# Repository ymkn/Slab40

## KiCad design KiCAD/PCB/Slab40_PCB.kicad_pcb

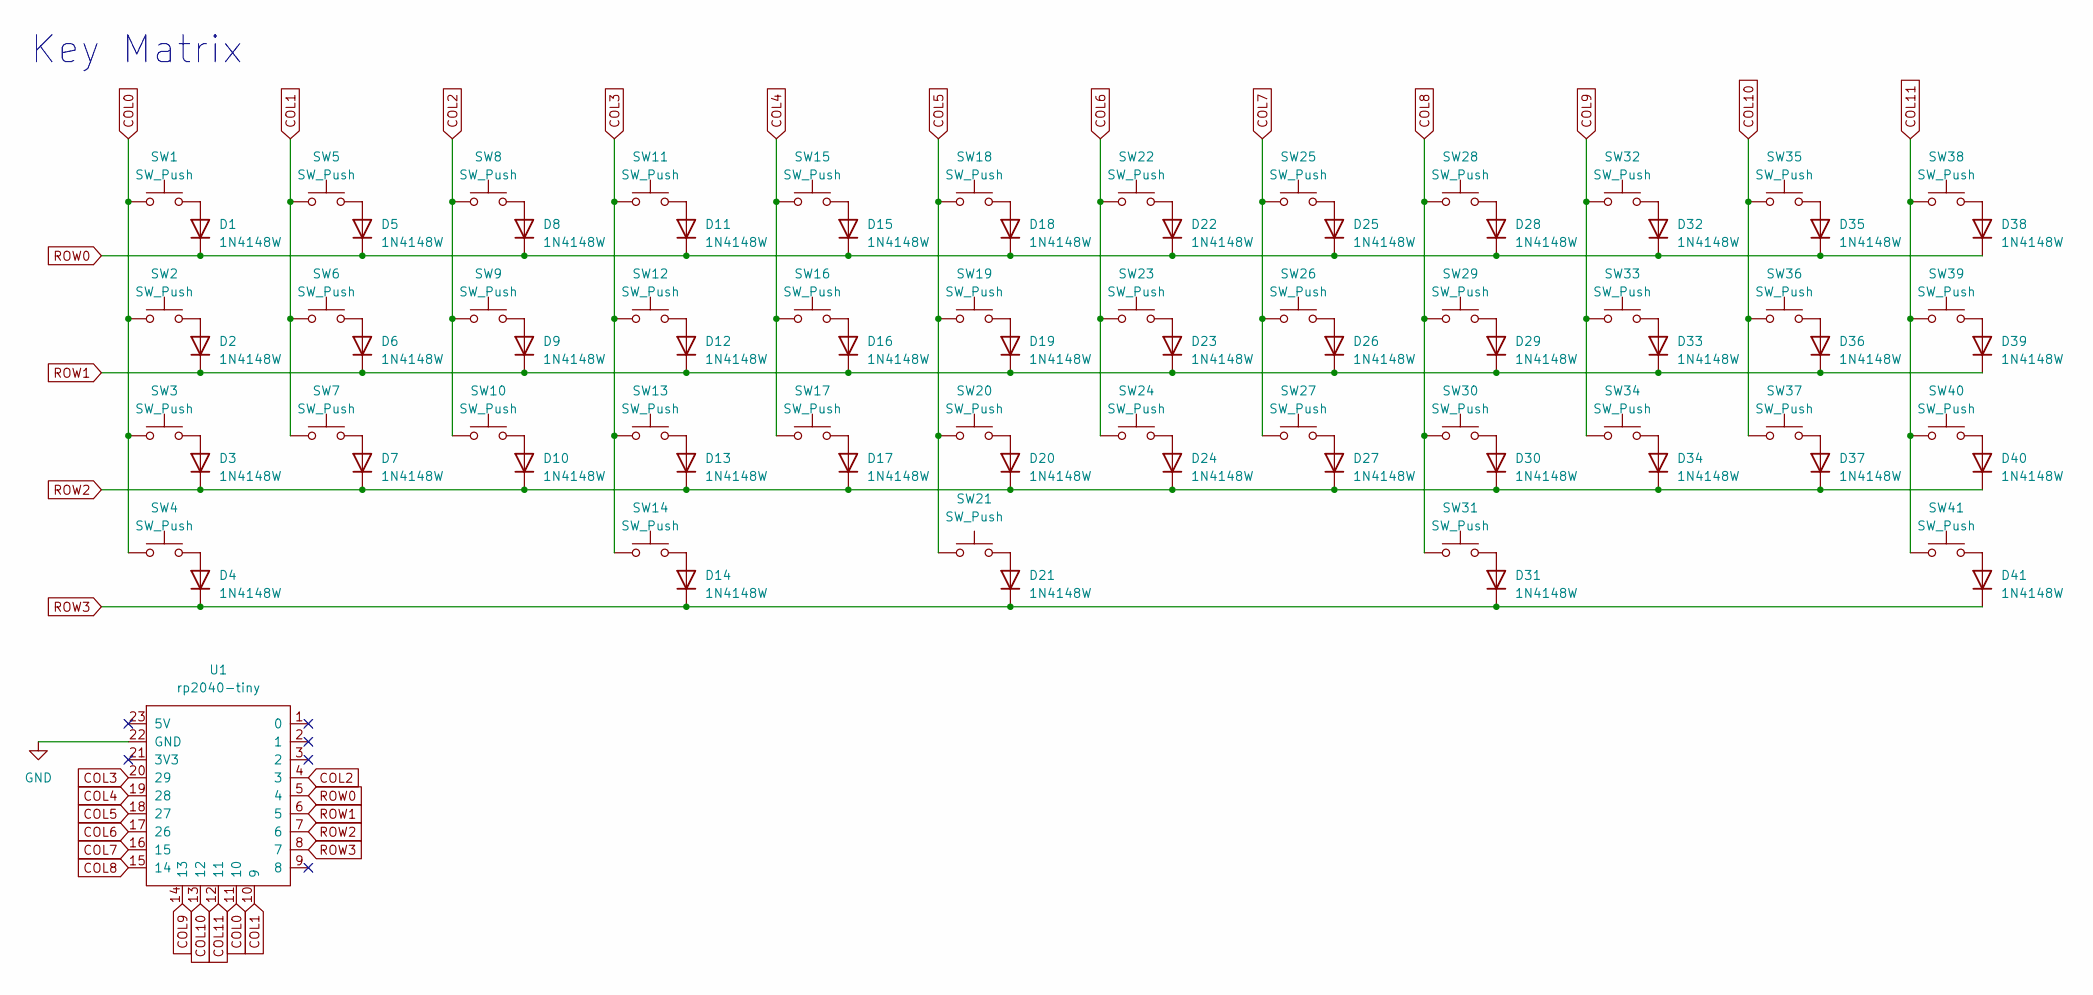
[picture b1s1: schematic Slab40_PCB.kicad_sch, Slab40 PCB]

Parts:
D1, D2, D3, D4, D5, D6, D7, D8, D9, D10, D11, D12, D13, D14, D15, D16, D17, D18, D19, D20, D21, D22, D23, D24, D25, D26, D27, D28, D29, D30, D31, D32, D33, D34, D35, D36, D37, D38, D39, D40, D41: 1N4148W; D_SOD-123; LCSC Parts # C81598
SW1, SW40: SW_Push; SW_MX_HS_CPG151101S11_1.25u
SW2, SW4, SW39, SW41: SW_Push; SW_MX_HS_CPG151101S11_1.5u
SW3, SW38: SW_Push; SW_MX_HS_CPG151101S11_1.75u
SW5, SW6, SW7, SW8, SW9, SW10, SW11, SW12, SW13, SW14, SW15, SW16, SW17, SW18, SW19, SW20, SW21, SW22, SW23, SW24, SW25, SW26, SW27, SW28, SW29, SW30, SW31, SW32, SW33, SW34, SW35, SW36, SW37: SW_Push; SW_MX_HS_CPG151101S11_1u
U1: rp2040-tiny; rp2040-tiny-smd

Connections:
COL0: SW1.1, SW2.1, SW3.1, SW4.1, U1.11 (10)
COL1: SW5.1, SW6.1, SW7.1, U1.10 (9)
COL2: SW8.1, SW9.1, SW10.1, U1.4 (3)
COL3: SW11.1, SW12.1, SW13.1, SW14.1, U1.20 (29)
COL4: SW15.1, SW16.1, SW17.1, U1.19 (28)
COL5: SW18.1, SW19.1, SW20.1, SW21.1, U1.18 (27)
COL6: SW22.1, SW23.1, SW24.1, U1.17 (26)
COL7: SW25.1, SW26.1, SW27.1, U1.16 (15)
COL8: SW28.1, SW29.1, SW30.1, SW31.1, U1.15 (14)
COL9: SW32.1, SW33.1, SW34.1, U1.14 (13)
COL10: SW35.1, SW36.1, SW37.1, U1.13 (12)
COL11: SW38.1, SW39.1, SW40.1, SW41.1, U1.12 (11)
GND: U1.22 (GND)
unnamed: D1.2 (A), SW1.2
unnamed: D2.2 (A), SW2.2
unnamed: D3.2 (A), SW3.2
unnamed: D4.2 (A), SW4.2
unnamed: D5.2 (A), SW5.2
unnamed: D6.2 (A), SW6.2
unnamed: D7.2 (A), SW7.2
unnamed: D8.2 (A), SW8.2
unnamed: D9.2 (A), SW9.2
unnamed: D10.2 (A), SW10.2
unnamed: D11.2 (A), SW11.2
unnamed: D12.2 (A), SW12.2
unnamed: D13.2 (A), SW13.2
unnamed: D14.2 (A), SW14.2
unnamed: D15.2 (A), SW15.2
unnamed: D16.2 (A), SW16.2
unnamed: D17.2 (A), SW17.2
unnamed: D18.2 (A), SW18.2
unnamed: D19.2 (A), SW19.2
unnamed: D20.2 (A), SW20.2
unnamed: D21.2 (A), SW21.2
unnamed: D22.2 (A), SW22.2
unnamed: D23.2 (A), SW23.2
unnamed: D24.2 (A), SW24.2
unnamed: D25.2 (A), SW25.2
unnamed: D26.2 (A), SW26.2
unnamed: D27.2 (A), SW27.2
unnamed: D28.2 (A), SW28.2
unnamed: D29.2 (A), SW29.2
unnamed: D30.2 (A), SW30.2
unnamed: D31.2 (A), SW31.2
unnamed: D32.2 (A), SW32.2
unnamed: D33.2 (A), SW33.2
unnamed: D34.2 (A), SW34.2
unnamed: D35.2 (A), SW35.2
unnamed: D36.2 (A), SW36.2
unnamed: D37.2 (A), SW37.2
unnamed: D38.2 (A), SW38.2
unnamed: D39.2 (A), SW39.2
unnamed: D40.2 (A), SW40.2
unnamed: D41.2 (A), SW41.2
ROW0: D1.1 (K), D5.1 (K), D8.1 (K), D11.1 (K), D15.1 (K), D18.1 (K), D22.1 (K), D25.1 (K), D28.1 (K), D32.1 (K), D35.1 (K), D38.1 (K), U1.5 (4)
ROW1: D2.1 (K), D6.1 (K), D9.1 (K), D12.1 (K), D16.1 (K), D19.1 (K), D23.1 (K), D26.1 (K), D29.1 (K), D33.1 (K), D36.1 (K), D39.1 (K), U1.6 (5)
ROW2: D3.1 (K), D7.1 (K), D10.1 (K), D13.1 (K), D17.1 (K), D20.1 (K), D24.1 (K), D27.1 (K), D30.1 (K), D34.1 (K), D37.1 (K), D40.1 (K), U1.7 (6)
ROW3: D4.1 (K), D14.1 (K), D21.1 (K), D31.1 (K), D41.1 (K), U1.8 (7)

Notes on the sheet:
Key Matrix

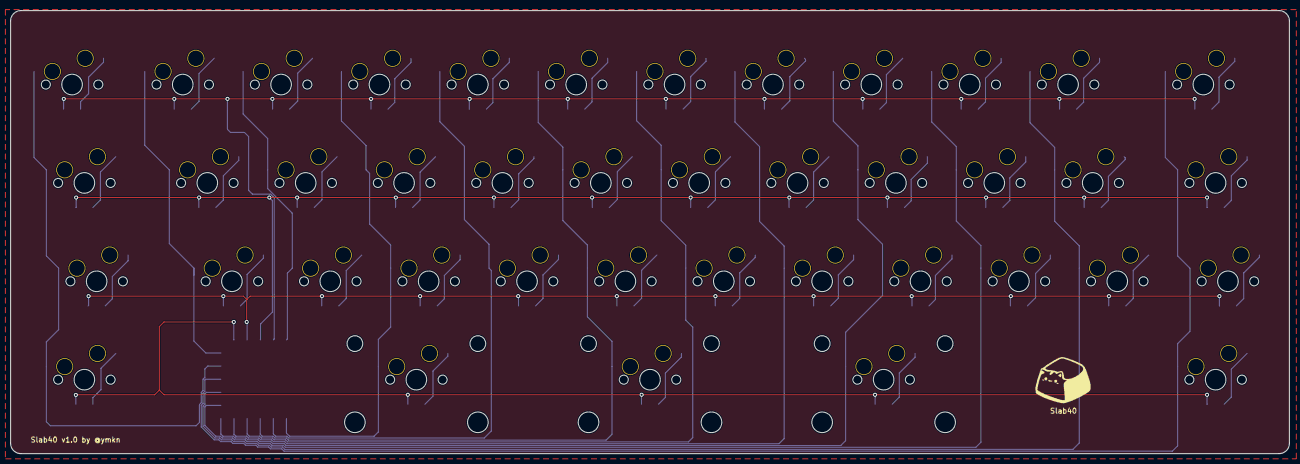
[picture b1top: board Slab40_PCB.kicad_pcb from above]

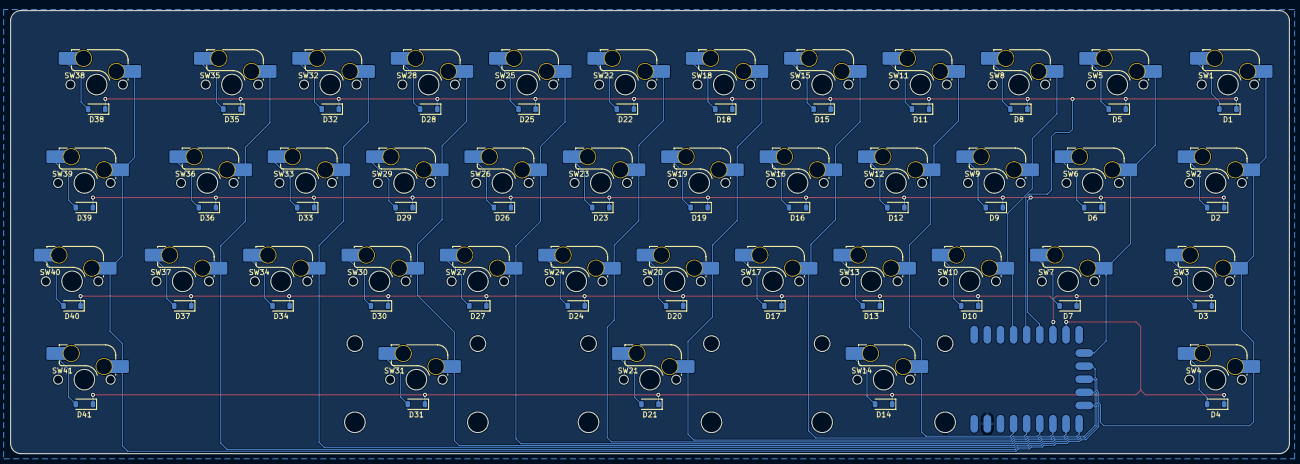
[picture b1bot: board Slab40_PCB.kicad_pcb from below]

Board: 2 copper layers, 247.6 x 85.8 mm, 83 parts (83 on the bottom side), 57 nets.

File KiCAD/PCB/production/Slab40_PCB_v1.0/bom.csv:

Designator,Footprint,Quantity,Value,LCSC Part #
"D1, D10, D11, D12, D13, D14, D15, D16, D17, D18, D19, D2, D20, D21, D22, D23, D24, D25, D26, D27, D28, D29, D3, D30, D31, D32, D33, D34, D35, D36, D37, D38, D39, D4, D40, D41, D5, D6, D7, D8, D9",D_SOD-123,41,1N4148W,
"SW1, SW40",SW_MX_HS_CPG151101S11_1.25u,2,SW_Push,
"SW10, SW11, SW12, SW13, SW14, SW15, SW16, SW17, SW18, SW19, SW20, SW21, SW22, SW23, SW24, SW25, SW26, SW27, SW28, SW29, SW30, SW31, SW32, SW33, SW34, SW35, SW36, SW37, SW5, SW6, SW7, SW8, SW9",SW_MX_HS_CPG151101S11_1u,33,SW_Push,
"SW2, SW39, SW4, SW41",SW_MX_HS_CPG151101S11_1.5u,4,SW_Push,
"SW3, SW38",SW_MX_HS_CPG151101S11_1.75u,2,SW_Push,
U1,rp2040-tiny-smd,1,rp2040-tiny,

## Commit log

2024-09-01 ディレクトリ構造の変更
2024-09-01 READMEとLICENSEの追加
2024-09-01 リリースファイルのリンク修正
2024-09-04 マージンを左右対称に調整
2024-09-14 スイッチパッドをオプションにしたためガイドを修正、その他加筆修正、ケースに関する記載を削除
